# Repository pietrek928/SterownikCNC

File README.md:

# SterownikCNC
Sterownik do frezarki CNC

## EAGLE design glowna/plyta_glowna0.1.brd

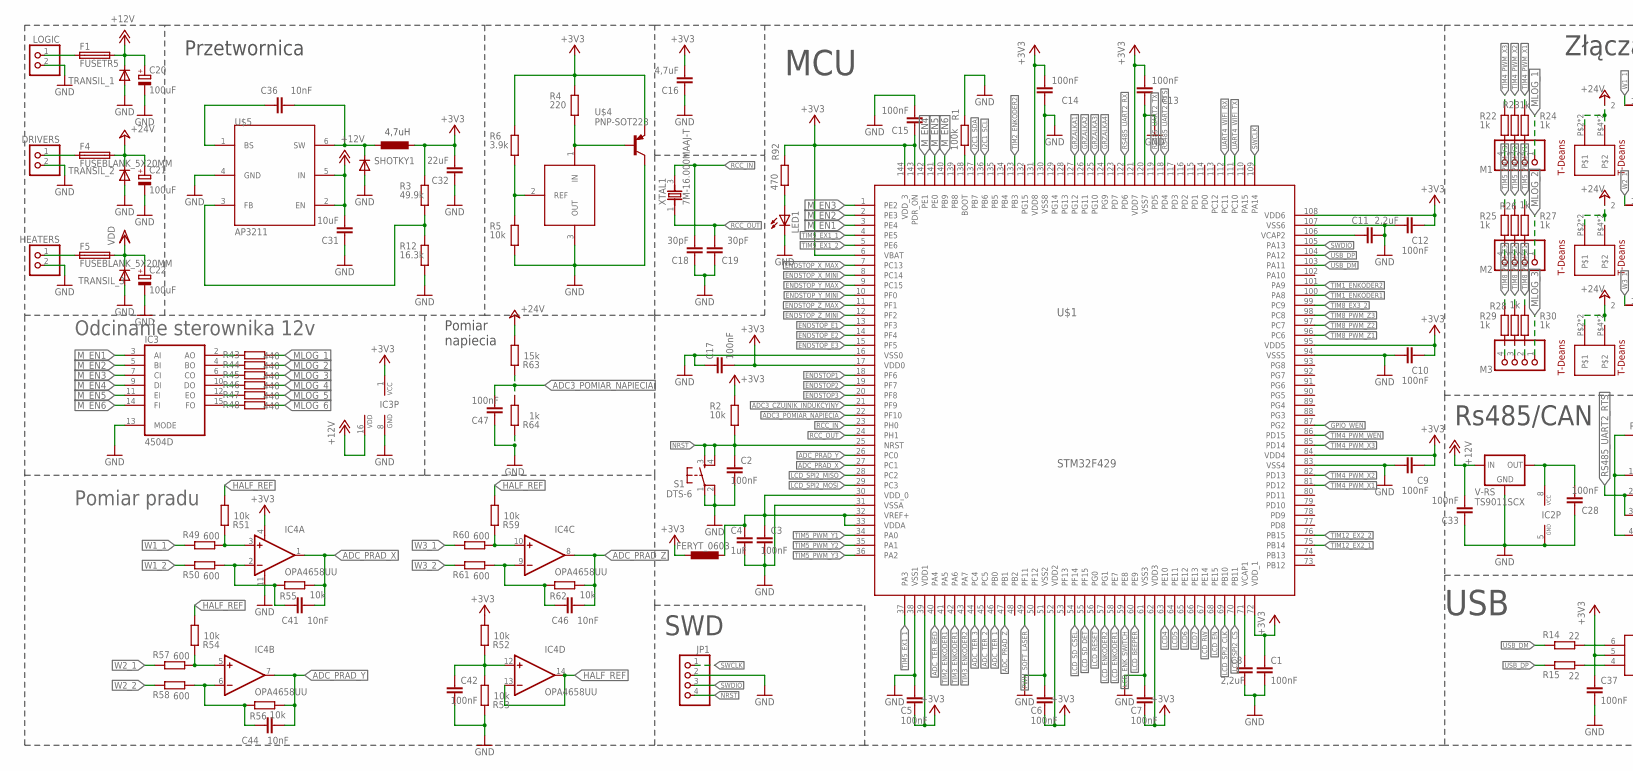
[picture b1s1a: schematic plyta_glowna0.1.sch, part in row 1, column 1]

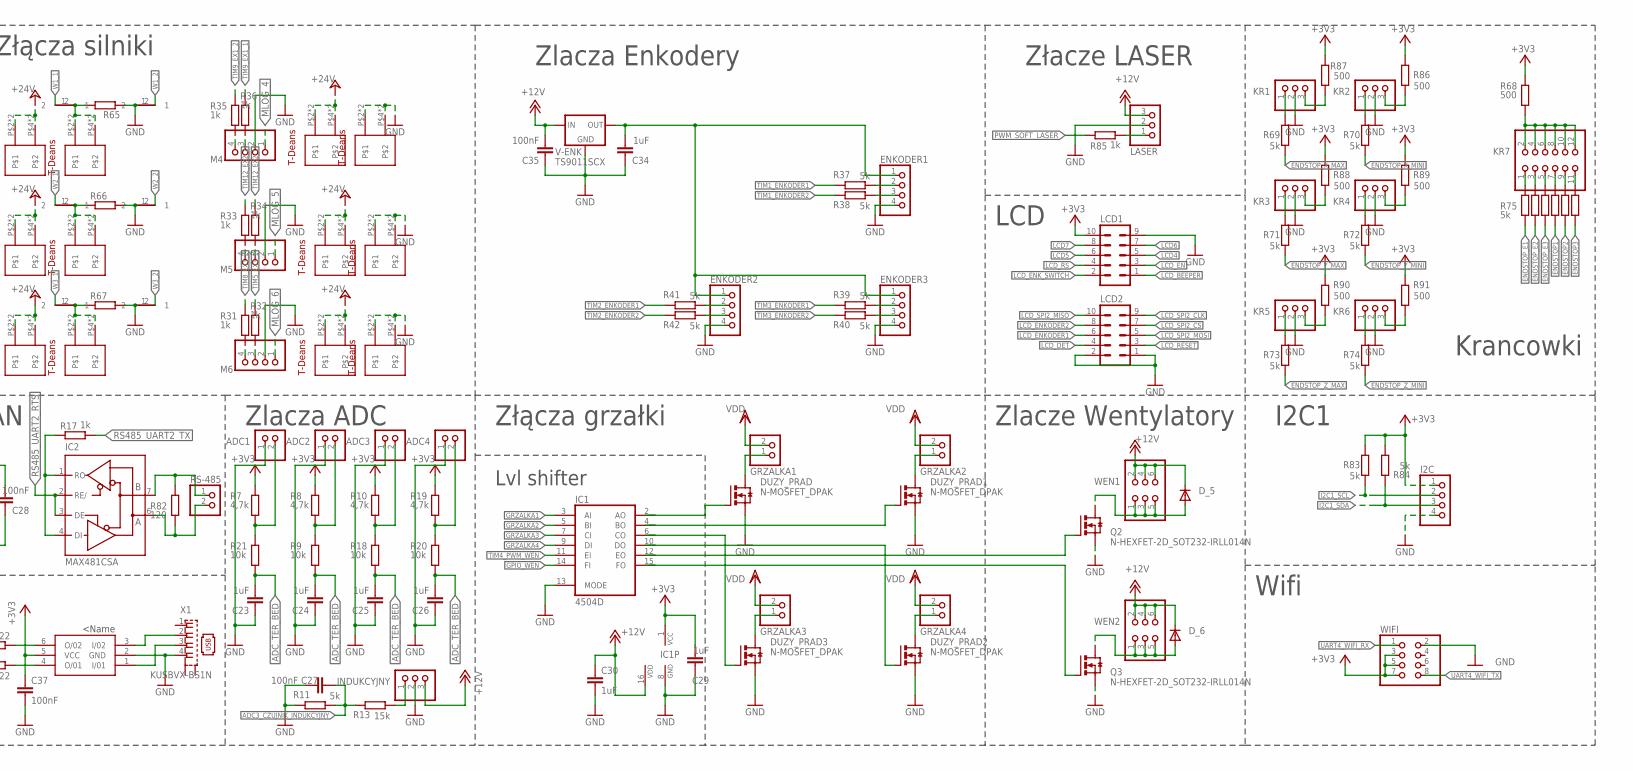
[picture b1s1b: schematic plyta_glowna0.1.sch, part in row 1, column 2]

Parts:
1, 2, 3, 4, 5, 6, 7, 8, 9, 10, 11, 12: PLYTKA_T
4,7UH: FERYT_0603; R0603
ADC1, ADC2, ADC3, ADC4: PINHD-1X2; 1X02
C1, C2, C3, C5, C6, C7, C9, C10, C12, C13, C14, C15, C17, C27, C28, C33, C35, C37, C42, C47: 100nF; C0603
C4, C23, C24, C25, C26, C29, C30, C34: 1uF; C0603
C8, C11: 2,2uF; C0603
C16: 4,7uF; C0603
C18, C19: 30pF; C0603
C20, C21, C22: 100uF; UD-8X10_NICHICON
C31: 10uF; C0603
C32: 22uF; C0603
C36, C41, C44, C46: 10nF; C0603
DRIVERS: PINHD-1X2; 1X02
DUZY_PRAD, DUZY_PRAD1, DUZY_PRAD2, DUZY_PRAD3: N-MOSFET_DPAK; D-PAK_TO252AA
D_5, D_6: DIODE-DO-214AC; DO-214AC
ENKODER1, ENKODER2, ENKODER3: PINHD-1X4; 1X04
F1: FUSETR5; TR5
F4, F5: FUSEBLANK_5X20MM; FUSE_HOLDER_5X20MM
GRZALKA1, GRZALKA2, GRZALKA3, GRZALKA4: PINHD-1X2; 1X02
HEATERS: PINHD-1X2; 1X02
I2C: PINHD-1X4; 1X04
IC1, IC3: 4504D; SO16
IC2: MAX481CSA; SO08
IC4: OPA4658UU; SO14
INDUKCYJNY: PINHD-1X3; 1X03
JP1: PINHD-1X4; 1X04
KR1, KR2, KR3, KR4, KR5, KR6: PINHD-1X3; 1X03
KR7: PINHD-2X6; 2X06
LASER: PINHD-1X3; 1X03
LCD1, LCD2: ML10
LED1: LEDSML0603; SML0603
LOGIC: PINHD-1X2; 1X02
M1, M2, M3, M4, M5, M6: PINHD-1X4; 1X04
Q2, Q3: N-HEXFET-2D_SOT232-IRLL014N; SOT223
R1: 100k; R0603
R2, R5, R9, R18, R20, R21, R51, R52, R53, R54, R55, R56, R59, R62: 10k; R0603
R3: 49.9k; R0603
R4: 220; R0603
R6: 3.9k; R0603
R7, R8, R10, R19: 4,7k; R0603
R11, R37, R38, R39, R40, R41, R42, R69, R70, R71, R72, R73, R74, R75, R76, R77, R78, R79, R80, R83, R84: 5k; R0603
R12: 16.3k; R0603
R13, R63: 15k; R0603
R14, R15: 22; R0603
R17, R22, R23, R24, R25, R26, R27, R28, R29, R30, R31, R32, R33, R34, R35, R36, R64, R85: 1k; R0603
R43, R44, R45, R46, R47, R48: 440; R0603
R49, R50, R57, R58, R60, R61: 600; R0603
R65, R66, R67: R-EU_R2512; R2512
R68, R86, R87, R88, R89, R90, R91: 500; R0603
R82: 120; R0603
R92: 470; R0603
RS-485: PINHD-1X2; 1X02
S1: DTS-6
SHOTKY1: DIODE-DO-214AC; DO-214AC
TRANSIL_1, TRANSIL_2, TRANSIL_3: DIODE-DO-214AC; DO-214AC
U$1: STM32F429; SQFP-S-20X20-144
U$2: FERYT_0603; R0603
U$3: TL431AIDBZR; SOT23
U$4: PNP-SOT223; SOT223
U$5: AP3211; TSOT23
U$6: USBLC6-2; SOT95P275X110-6N
U$20, U$21, U$22, U$23, U$24, U$25: SEPARATOR
V-ENK: TS9011SCX; SOT23
V-RS: TS9011SCX; SOT23
WEN1, WEN2: PINHD-2X3; 2X03
WIFI: PINHD-2X4; 2X04
X1: KUSBVX-BS1N
XTAL1: 7M-16.000MAAJ-T; TXC_7M-16.000MAAJ-T

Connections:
+3V3: 4,7UH.2, C1.1, C5.2, C6.2, C7.2, C9.2, C10.2, C12.2, C13.2, C14.2, C15.1, C16.2, C17.2, C29.2, C32.2, C37.1, I2C.1, IC1.1 (VCC), IC3.1 (VCC), IC4.4 (V+), LCD1.10, R2.1, R3.1, R4.1, R6.1, R7.1, R8.1, R10.1, R19.1, R52.2, R68.2, R83.2, R84.2, R86.1, R87.1, R88.1, R89.1, R90.1, R91.1, R92.1, U$1.6 (VBAT), U$1.17 (VDD0), U$1.39 (VDD1), U$1.52 (VDD2), U$1.62 (VDD3), U$1.72 (VDD_1), U$1.84 (VDD4), U$1.95 (VDD5), U$1.108 (VDD6), U$1.121 (VDD7), U$1.131 (VDD8), U$1.143 (PDR_ON), U$1.144 (VDD_3), U$2.1, U$4.3 (E), U$6.5 (VCC), WIFI.3, WIFI.5, WIFI.7
+12V: C20.+, C30.1, C31.2, C33.2, C35.2, D_5.C, D_6.C, F1.2, IC1.16 (VDD), IC3.16 (VDD), INDUKCYJNY.3, LASER.3, TRANSIL_1.C, U$5.2 (EN), U$5.5 (IN), V-ENK.3 (IN), V-RS.3 (IN), WEN1.2, WEN1.4, WEN1.6, WEN2.2, WEN2.4, WEN2.6
+24V: 1.P$2, 1.P$3, 1.P$4, 1.P$5, 3.P$2, 3.P$3, 3.P$4, 3.P$5, 5.P$2, 5.P$3, 5.P$4, 5.P$5, 7.P$2, 7.P$3, 7.P$4, 7.P$5, 9.P$2, 9.P$3, 9.P$4, 9.P$5, 11.P$2, 11.P$3, 11.P$4, 11.P$5, C21.+, F4.2, R63.2, TRANSIL_2.C
ADC3_CZUJNIK_INDUKCYJNY: U$1.21 (PF9)
ADC3_POMIAR_NAPIECIA: C47.2, R63.1, R64.2, U$1.22 (PF10)
ADC_PRAD_X: C41.2, IC4.1 (OUT), R55.1, U$1.27 (PC1)
ADC_PRAD_Y: C44.2, IC4.7 (OUT), R56.1, U$1.26 (PC0)
ADC_PRAD_Z: C46.2, IC4.8 (OUT), R62.1, U$1.47 (PB1)
ADC_TER_1: U$1.46 (PB0)
ADC_TER_2: U$1.45 (PC5)
ADC_TER_3: U$1.44 (PC4)
ADC_TER_BED: C23.2, C24.2, C25.2, C26.2, R9.2, R18.2, R20.2, R21.2, U$1.40 (PA4)
ENDSTOP1: R78.2, U$1.18 (PF6)
ENDSTOP2: R79.2, U$1.19 (PF7)
ENDSTOP3: R80.2, U$1.20 (PF8)
ENDSTOP_E1: R75.2, U$1.13 (PF3)
ENDSTOP_E2: R76.2, U$1.14 (PF4)
ENDSTOP_E3: R77.2, U$1.15 (PF5)
ENDSTOP_X_MAX: R69.1, U$1.7 (PC13)
ENDSTOP_X_MINI: R70.1, U$1.8 (PC14)
ENDSTOP_Y_MAX: R71.1, U$1.9 (PC15)
ENDSTOP_Y_MINI: R72.1, U$1.10 (PF0)
ENDSTOP_Z_MAX: R73.1, U$1.11 (PF1)
ENDSTOP_Z_MINI: R74.1, U$1.12 (PF2)
GND: 8.P$2, 8.P$3, 8.P$4, 8.P$5, 10.P$2, 10.P$3, 10.P$4, 10.P$5, 12.P$2, 12.P$3, 12.P$4, 12.P$5, ADC1.1, ADC2.1, ADC3.1, ADC4.1, C1.2, C2.2, C3.2, C4.2, C5.1, C6.1, C7.1, C8.2, C9.1, C10.1, C11.2, C12.1, C13.1, C14.1, C15.2, C16.1, C17.1, C18.1, C19.1, C20.-, C21.-, C22.-, C23.1, C24.1, C25.1, C26.1, C27.2, C28.1, C29.1, C30.2, C31.1, C32.1, C33.1, C34.1, C35.1, C37.2, C42.2, C47.1, DRIVERS.2, DUZY_PRAD.3 (S), DUZY_PRAD1.3 (S), DUZY_PRAD2.3 (S), DUZY_PRAD3.3 (S), ENKODER1.4, ENKODER2.4, ENKODER3.4, HEATERS.2, I2C.4, IC1.8 (GND), IC1.13 (MODE), IC2.5 (GND), IC3.8 (GND), IC3.13 (MODE), IC4.11 (V-), INDUKCYJNY.2, JP1.2, KR1.2, KR2.2, KR3.2, KR4.2, KR5.2, KR6.2, LASER.2, LCD1.9, LCD2.1, LCD2.2, LED1.C, LOGIC.2, M4.2, M5.2, M6.2, Q2.3 (S), Q3.3 (S), R1.1, R5.2, R11.1, R12.2, R53.1, R64.1, R65.1, R66.2, R67.2, S1.1, S1.2, SHOTKY1.A, TRANSIL_1.A, TRANSIL_2.A, TRANSIL_3.A, U$1.16 (VSS0), U$1.31 (VSSA), U$1.38 (VSS1), U$1.51 (VSS2), U$1.61 (VSS3), U$1.83 (VSS4), U$1.94 (VSS5), U$1.107 (VSS6), U$1.120 (VSS7), U$1.130 (VSS8), U$3.3 (OUT), U$4.2 (C), U$4.4 (C), U$5.4 (GND), U$6.2 (GND), U$20.1, U$21.1, U$22.1, V-ENK.1 (GND), V-RS.1 (GND), WIFI.2, X1.4
GPIO_WEN: IC1.14 (FI), U$1.87 (PG2)
GRZALKA1: IC1.3 (AI), U$1.127 (PG12)
GRZALKA2: IC1.5 (BI), U$1.126 (PG11)
GRZALKA3: IC1.7 (CI), U$1.125 (PG10)
GRZALKA4: IC1.9 (DI), U$1.124 (PG9)
HALF_REF: IC4.13 (-IN), IC4.14 (OUT), R51.2, R54.2, R59.2
I2C1_SCL: I2C.2, R83.1, U$1.136 (PB6)
I2C1_SDA: I2C.3, R84.1, U$1.137 (PB7)
LCD4: LCD1.5, U$1.63 (PE10)
LCD5: LCD1.6, U$1.64 (PE11)
LCD6: LCD1.7, U$1.65 (PE12)
LCD7: LCD1.8, U$1.66 (PE13)
LCD_BEEPER: LCD1.1, U$1.60 (PE9)
LCD_DET: LCD2.4
LCD_EN: LCD1.3, U$1.68 (PE15)
LCD_ENKODER1: LCD2.6, U$1.58 (PE7)
LCD_ENKODER2: LCD2.8, U$1.57 (PG1)
LCD_ENK_SWITCH: LCD1.2, U$1.59 (PE8)
LCD_RESET: LCD2.3, U$1.56 (PG0)
LCD_RS: LCD1.4
LCD_RW: U$1.67 (PE14)
LCD_SD_CSEL: U$1.54 (PF14)
LCD_SD_DET: U$1.55 (PF15)
LCD_SPI2_CLK: LCD2.9, U$1.69 (PB10)
LCD_SPI2_CS: LCD2.7, U$1.70 (PB11)
LCD_SPI2_MISO: LCD2.10, U$1.28 (PC2)
LCD_SPI2_MOSI: LCD2.5, U$1.29 (PC3)
MLOG_1: M1.1, R43.2
MLOG_2: M2.1, R44.2
MLOG_3: M3.1, R45.2
MLOG_4: M4.1, R46.2
MLOG_5: M5.1, R47.2
MLOG_6: M6.1, R48.2
M_EN1: IC3.3 (AI)
M_EN3: U$1.1 (PE2)
unnamed: 4,7UH.1, C36.1, SHOTKY1.C, U$5.6 (SW)
unnamed: C8.1, U$1.71 (VCAP1)
unnamed: R3.2, R12.1, U$5.3 (FB)
unnamed: R14.2, U$6.6 (O/02)
unnamed: C3.1, C4.1, U$1.30 (VDD_0), U$1.32 (VREF+), U$1.33 (VDDA), U$2.2
unnamed: R5.1, R6.2, U$3.2 (REF)
unnamed: F1.1, LOGIC.1
unnamed: DRIVERS.1, F4.1
unnamed: R4.2, U$3.1 (IN), U$4.1 (B)
unnamed: F5.1, HEATERS.1
unnamed: D_6.A, Q3.2 (D), Q3.4 (D), WEN2.1, WEN2.3, WEN2.5
unnamed: DUZY_PRAD.4 (D), GRZALKA1.1
unnamed: R15.2, U$6.4 (O/01)
unnamed: D_5.A, Q2.2 (D), Q2.4 (D), WEN1.1, WEN1.3, WEN1.5
unnamed: U$6.1 (I/01), X1.3
unnamed: DUZY_PRAD1.4 (D), GRZALKA2.1
unnamed: DUZY_PRAD2.4 (D), GRZALKA4.1
unnamed: C11.1, U$1.106 (VCAP2)
unnamed: DUZY_PRAD3.4 (D), GRZALKA3.1
unnamed: DUZY_PRAD.1 (G), IC1.2 (AO)
unnamed: KR1.1, R69.2
unnamed: LASER.1, R85.1
unnamed: KR3.1, R71.2
unnamed: KR2.1, R70.2
unnamed: R1.2, U$1.138 (BOOT)
unnamed: KR4.1, R72.2
unnamed: KR6.1, R74.2
unnamed: KR5.1, R73.2
unnamed: IC2.7 (B), R82.1, RS-485.1
unnamed: IC2.6 (A), R82.2, RS-485.2
unnamed: KR7.1, R75.1
unnamed: DUZY_PRAD1.1 (G), IC1.4 (BO)
unnamed: DUZY_PRAD3.1 (G), IC1.6 (CO)
unnamed: DUZY_PRAD2.1 (G), IC1.10 (DO)
unnamed: IC1.12 (EO), Q2.1 (G)
unnamed: IC1.15 (FO), Q3.1 (G)
unnamed: INDUKCYJNY.1, R13.2
unnamed: C36.2, U$5.1 (BS)
unnamed: C28.2, IC2.8 (VCC), V-RS.2 (OUT)
unnamed: M1.4, R22.2
unnamed: ADC2.2, R8.2, R9.1
unnamed: ADC1.2, R7.2, R21.1
unnamed: ADC3.2, R10.2, R18.1
unnamed: M1.3, R23.2
unnamed: M1.2, R24.2
unnamed: ADC4.2, R19.2, R20.1
unnamed: M6.4, R31.2
unnamed: M2.4, R25.2
unnamed: M2.3, R26.2
unnamed: M6.3, R32.2
unnamed: M3.4, R29.2
unnamed: M3.3, R28.2
unnamed: U$6.3 (I/02), X1.2
unnamed: M5.4, R33.2
unnamed: M5.3, R34.2
unnamed: M2.2, R27.2
unnamed: M4.4, R35.2
unnamed: M4.3, R36.2
unnamed: ENKODER1.2, R37.2
unnamed: ENKODER1.3, R38.2
unnamed: ENKODER3.2, R39.2
unnamed: ENKODER3.3, R40.2
unnamed: ENKODER2.2, R41.2
unnamed: ENKODER2.3, R42.2
unnamed: IC3.2 (AO), R43.1
unnamed: IC3.4 (BO), R44.1
unnamed: IC3.6 (CO), R45.1
unnamed: IC3.10 (DO), R46.1
unnamed: IC3.12 (EO), R47.1
unnamed: IC3.15 (FO), R48.1
unnamed: IC4.3 (+IN), R49.2, R51.1
unnamed: C42.1, IC4.12 (+IN), R52.1, R53.2
unnamed: C41.1, IC4.2 (-IN), R50.2, R55.2
unnamed: C46.1, IC4.9 (-IN), R61.2, R62.2
unnamed: 2.P$2, 2.P$3, 2.P$4, 2.P$5, R65.2, U$23.2
unnamed: 4.P$2, 4.P$3, 4.P$4, 4.P$5, R66.1, U$24.2
unnamed: IC4.10 (+IN), R59.1, R60.2
unnamed: C44.1, IC4.6 (-IN), R56.2, R58.2
unnamed: IC4.5 (+IN), R54.1, R57.2
unnamed: 6.P$2, 6.P$3, 6.P$4, 6.P$5, R67.1, U$25.2
unnamed: KR7.3, R76.1
unnamed: KR7.5, R77.1
unnamed: KR7.7, R78.1
unnamed: KR7.9, R79.1
unnamed: KR7.11, R80.1
unnamed: KR7.2, KR7.4, KR7.6, KR7.8, KR7.10, KR7.12, R68.1
unnamed: KR1.3, R87.2
unnamed: KR2.3, R86.2
unnamed: KR3.3, R88.2
unnamed: KR4.3, R89.2
unnamed: KR5.3, R90.2
unnamed: KR6.3, R91.2
unnamed: C27.1, R11.2, R13.1
unnamed: LED1.A, R92.2
unnamed: C34.2, ENKODER1.1, ENKODER2.1, ENKODER3.1, V-ENK.2 (OUT)
NRST: C2.1, JP1.4, R2.2, S1.3, S1.4, U$1.25 (NRST)
PWM_SOFT_LASER: R85.2, U$1.49 (PF11)
RCC_IN: C18.2, U$1.23 (PH0), XTAL1.3
RCC_OUT: C19.2, U$1.24 (PH1), XTAL1.1
RS485_UART2_RTS: IC2.2 (RE/), IC2.3 (DE), U$1.118 (PD4)
RS485_UART2_RX: U$1.122 (PD6)
RS485_UART2_TX: IC2.1 (RO), IC2.4 (DI), R17.1, R17.2, U$1.119 (PD5)
SWCLK: JP1.1, U$1.109 (PA14)
SWDIO: JP1.3, U$1.105 (PA13)
TIM1_ENKODER1: R37.1, U$1.100 (PA8)
TIM1_ENKODER2: R38.1, U$1.101 (PA9)
TIM2_ENKODER1: R41.1, U$1.41 (PA5)
TIM2_ENKODER2: R42.1, U$1.133 (PB3)
TIM3_ENKODER1: R39.1, U$1.42 (PA6)
TIM3_ENKODER2: R40.1, U$1.43 (PA7)
TIM4_PWM_WEN: IC1.11 (EI), U$1.86 (PD15)
TIM4_PWM_X1: R24.1, U$1.81 (PD12)
TIM4_PWM_X2: R23.1, U$1.82 (PD13)
TIM4_PWM_X3: R22.1, U$1.85 (PD14)
TIM5_EX1_1: U$1.37 (PA3)
TIM5_EX3_1: R32.1
TIM5_PWM_Y1: R27.1, U$1.34 (PA0)
TIM5_PWM_Y2: R26.1, U$1.35 (PA1)
TIM5_PWM_Y3: R25.1, U$1.36 (PA2)
TIM8_EX3_2: R31.1, U$1.99 (PC9)
TIM8_PWM_Z1: M3.2, R30.1, R30.2, U$1.96 (PC6)
TIM8_PWM_Z2: R28.1, U$1.97 (PC7)
TIM8_PWM_Z3: R29.1, U$1.98 (PC8)
TIM9_EX1_1: R36.1, U$1.4 (PE5)
TIM9_EX1_2: R35.1, U$1.5 (PE6)
TIM12_EX2_1: R34.1, U$1.75 (PB14)
TIM12_EX2_2: R33.1, U$1.76 (PB15)
UART4_WIFI_RX: U$1.112 (PC11), WIFI.1
UART4_WIFI_TX: U$1.111 (PC10), WIFI.8
USB_DM: R14.1, U$1.103 (PA11)
USB_DP: R15.1, U$1.104 (PA12)
VDD: C22.+, F5.2, GRZALKA1.2, GRZALKA2.2, GRZALKA3.2, GRZALKA4.2, TRANSIL_3.C
W1_1: R49.1, U$23.1
W1_2: R50.1, U$20.2
W2_1: R57.1, U$24.1
W2_2: R58.1, U$21.2
W3_1: R60.1, U$25.1
W3_2: R61.1, U$22.2

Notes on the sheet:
MCU
Złącza silniki
Złącza grzałki
Zlacza ADC
Zlacza Enkodery
Rs485/CAN
Złacze LASER
Zlacze Wentylatory
USB
LCD
Krancowki
I2C1
Wifi
Lvl shifter
Pomiar napiecia
Pomiar pradu
Odcinanie sterownika 12v
SWD
Przetwornica
4,7uH

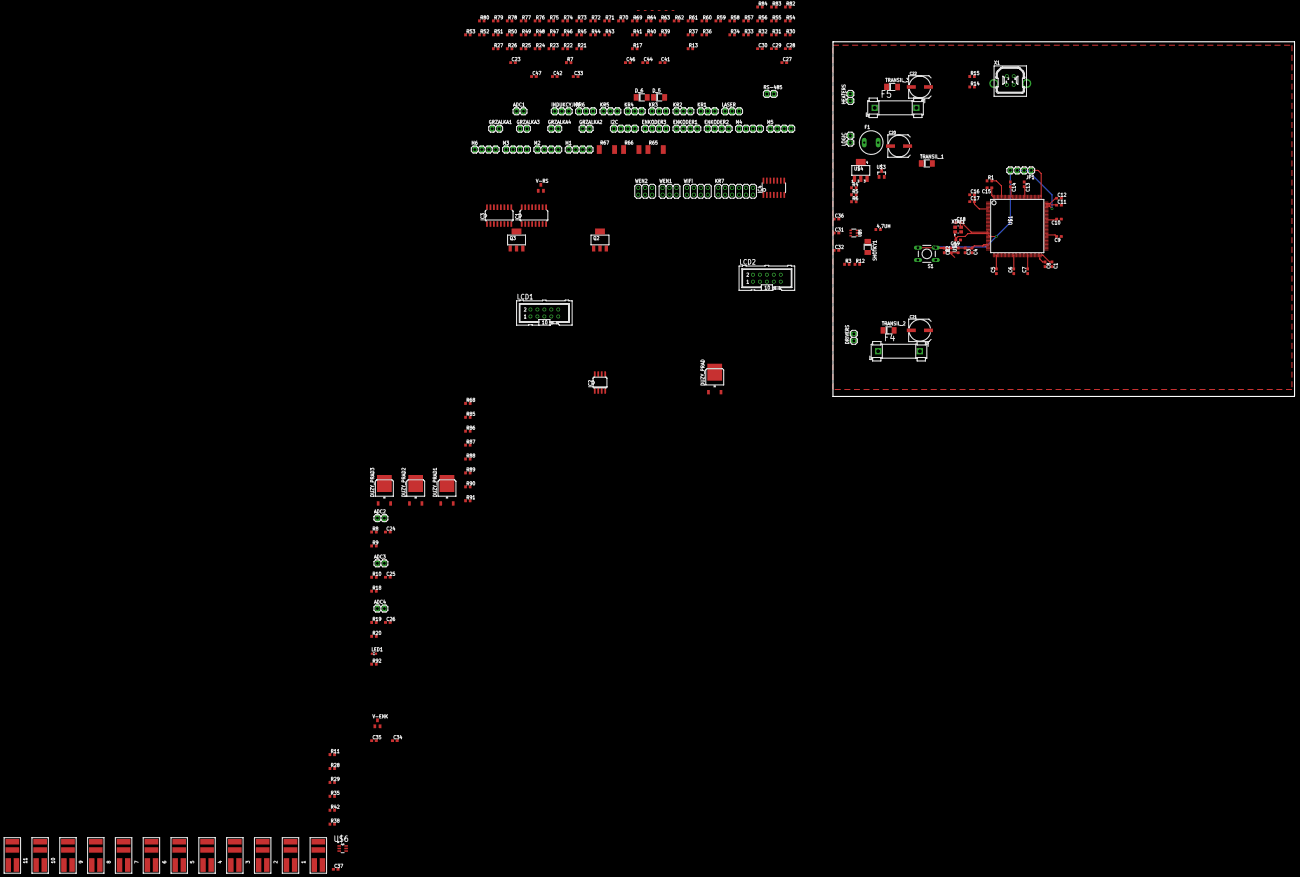
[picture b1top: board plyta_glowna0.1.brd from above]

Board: 2 copper layers, 168.6 x 129.5 mm, 219 parts (0 on the bottom side), 184 nets.

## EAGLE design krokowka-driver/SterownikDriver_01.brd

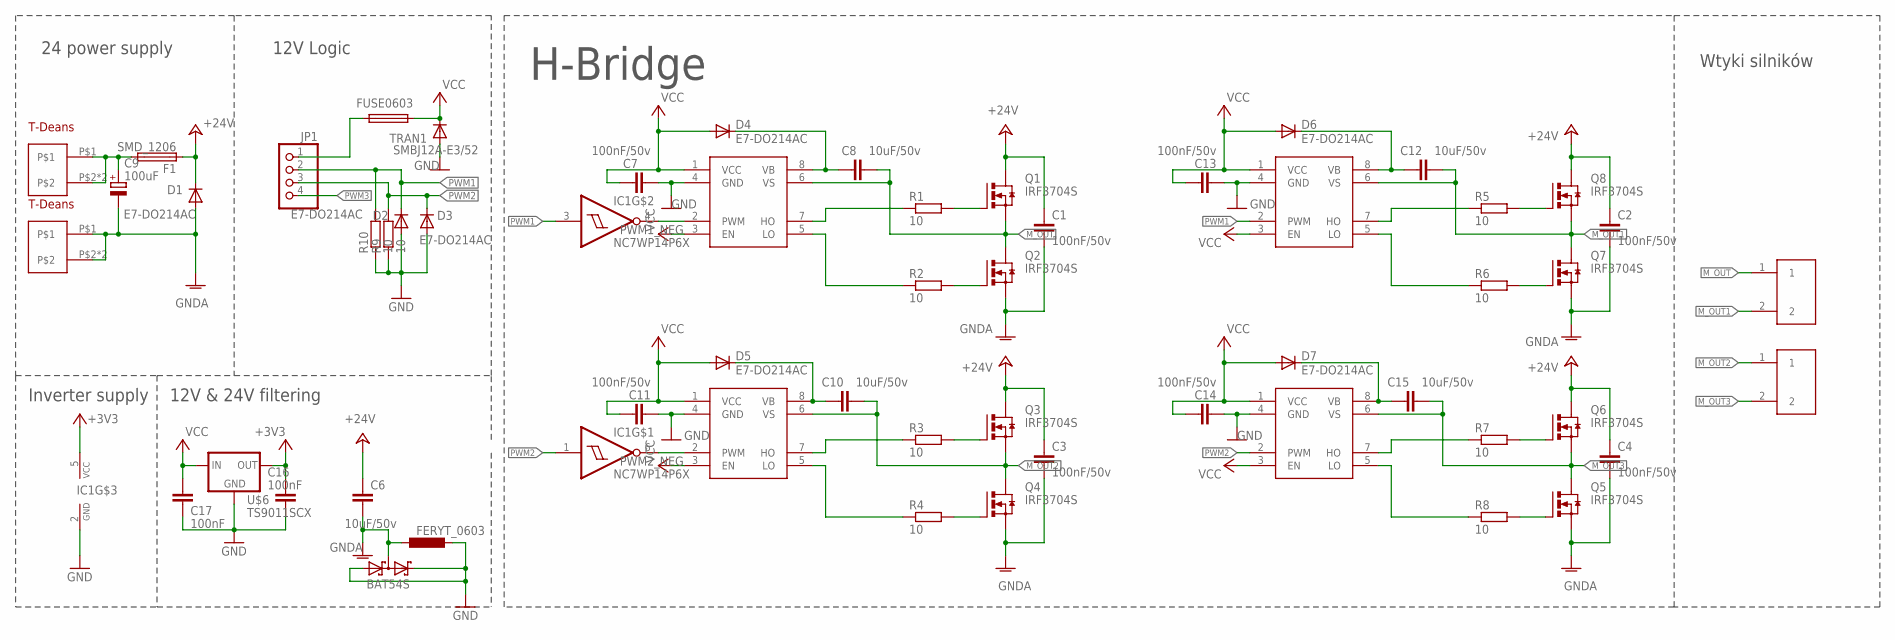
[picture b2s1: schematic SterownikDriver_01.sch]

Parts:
C1, C2, C3, C4, C7, C11, C13, C14: 100nF/50v; C0603K
C6, C8, C10, C12, C15: 10uF/50v; C0603K
C9: 100uF; 140CLH-0810
C16, C17: 100nF; C0603K
D1, D2, D3, D4, D5, D6, D7: E7-DO214AC; DO214AC
D8: BAT54S; SOT23
F1: SMD_1206; 1026
GND: T-DEANS
IC1: NC7WP14P6X; SOT65P210X110-6AN_SC88_SC70-6
JP1: PINHD-1X4; 1X04
Q1, Q2, Q3, Q4, Q5, Q6, Q7, Q8: IRF3704S; D2PACK
R1, R2, R3, R4, R5, R6, R7, R8, R9, R10: 10; R0603
TRAN1: SMBJ12A-E3/52; DO214AA
U1, U2, U3, U4: IR2104; SO08
U$3: FUSE0603; 0603
U$4: FERYT_0603; R0603
U$6: TS9011SCX; SOT23
U$7, U$9: PTB-02_5.08MM; PTB-5.08MM-02
VCC: T-DEANS

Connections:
+3V3: C16.1, IC1.5 (VCC), U$6.2 (OUT)
+24V: C1.1, C2.1, C3.1, C4.1, C6.1, D1.C, F1.P$1 (1), Q1.2 (D), Q3.2 (D), Q6.2 (D), Q8.2 (D)
F2: JP1.1, U$3.1
GND: C7.2, C11.2, C13.2, C14.2, C16.2, C17.2, D2.A, D3.A, D8.1 (A1), D8.2 (C2), IC1.2 (GND), R9.1, R10.1, TRAN1.A, U1.4 (GND), U2.4 (GND), U3.4 (GND), U4.4 (GND), U$4.2, U$6.1 (GND)
GNDA: C1.2, C2.2, C3.2, C4.2, C6.2, C9.-, D1.A, D8.3 (C1A2), GND.P$1, GND.P$2, GND.P$3, Q2.3 (S), Q4.3 (S), Q5.3 (S), Q7.3 (S), U$4.1
M_OUT: C8.2, Q1.3 (S), Q2.2 (D), U1.6 (VS), U$7.1
M_OUT1: C12.2, Q7.2 (D), Q8.3 (S), U2.6 (VS), U$7.2
M_OUT2: C10.2, Q3.3 (S), Q4.2 (D), U3.6 (VS), U$9.1
M_OUT3: C15.2, Q5.2 (D), Q6.3 (S), U4.6 (VS), U$9.2
unnamed: Q1.1 (G), R1.2
unnamed: Q2.1 (G), R2.2
unnamed: R1.1, U1.7 (HO)
unnamed: R2.1, U1.5 (LO)
unnamed: R5.1, U2.7 (HO)
unnamed: R6.1, U2.5 (LO)
unnamed: Q7.1 (G), R6.2
unnamed: Q8.1 (G), R5.2
unnamed: C10.1, D5.C, U3.8 (VB)
unnamed: C9.+, F1.P$2 (2), VCC.P$1, VCC.P$2, VCC.P$3
unnamed: R3.1, U3.7 (HO)
unnamed: R4.1, U3.5 (LO)
unnamed: Q4.1 (G), R4.2
unnamed: Q3.1 (G), R3.2
unnamed: C15.1, D7.C, U4.8 (VB)
unnamed: R7.1, U4.7 (HO)
unnamed: R8.1, U4.5 (LO)
unnamed: Q5.1 (G), R8.2
unnamed: Q6.1 (G), R7.2
unnamed: C8.1, D4.C, U1.8 (VB)
unnamed: C12.1, D6.C, U2.8 (VB)
PWM1: D2.C, IC1.3 (I), JP1.2, R10.2, U2.2 (PWM)
PWM1_NEG: IC1.4 (O), U1.2 (PWM)
PWM2: D3.C, IC1.1 (I), JP1.3, R9.2, U4.2 (PWM)
PWM2_NEG: IC1.6 (O), U3.2 (PWM)
PWM3: JP1.4
VCC: C7.1, C11.1, C13.1, C14.1, C17.1, D4.A, D5.A, D6.A, D7.A, TRAN1.C, U1.1 (VCC), U1.3 (EN), U2.1 (VCC), U2.3 (EN), U3.1 (VCC), U3.3 (EN), U4.1 (VCC), U4.3 (EN), U$3.2, U$6.3 (IN)

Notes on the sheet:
H-Bridge
Inverter supply
24 power supply
12V Logic
12V & 24V filtering
Wtyki silników

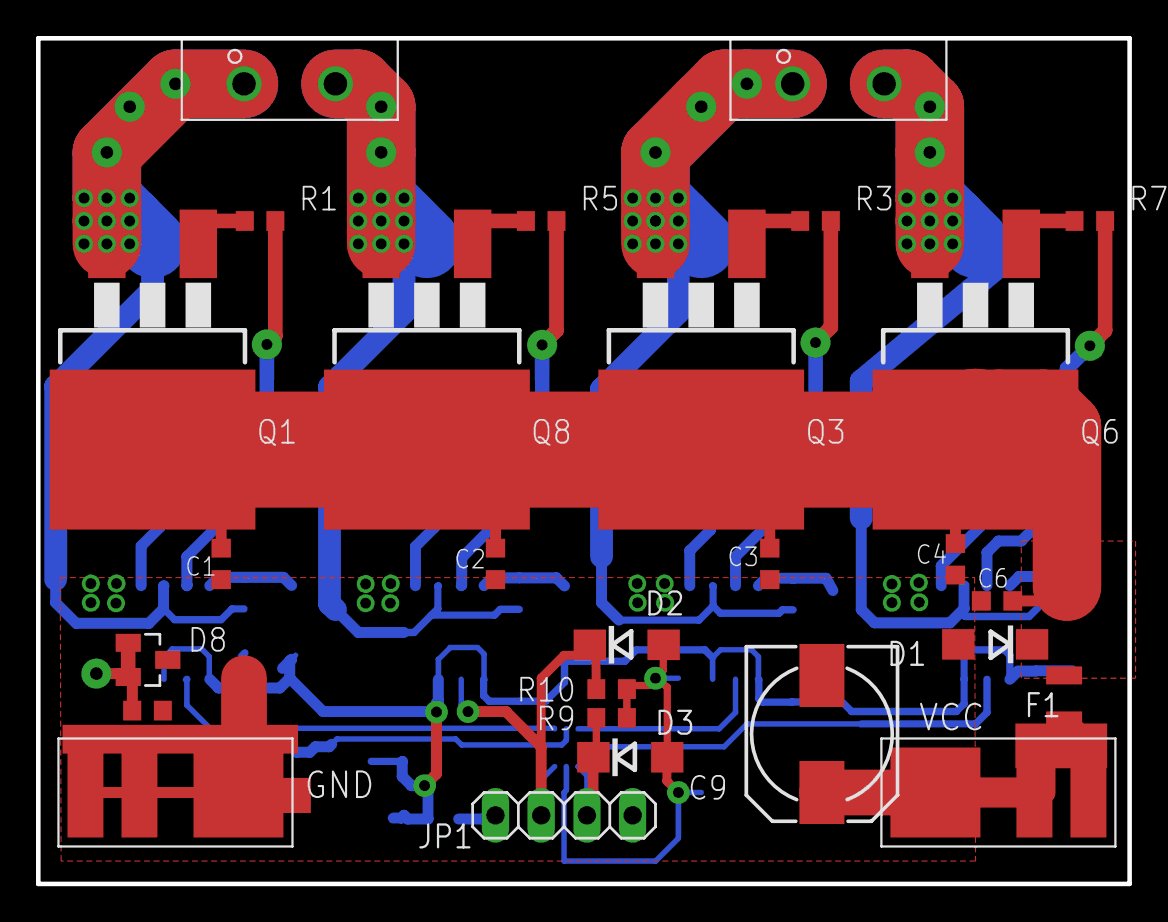
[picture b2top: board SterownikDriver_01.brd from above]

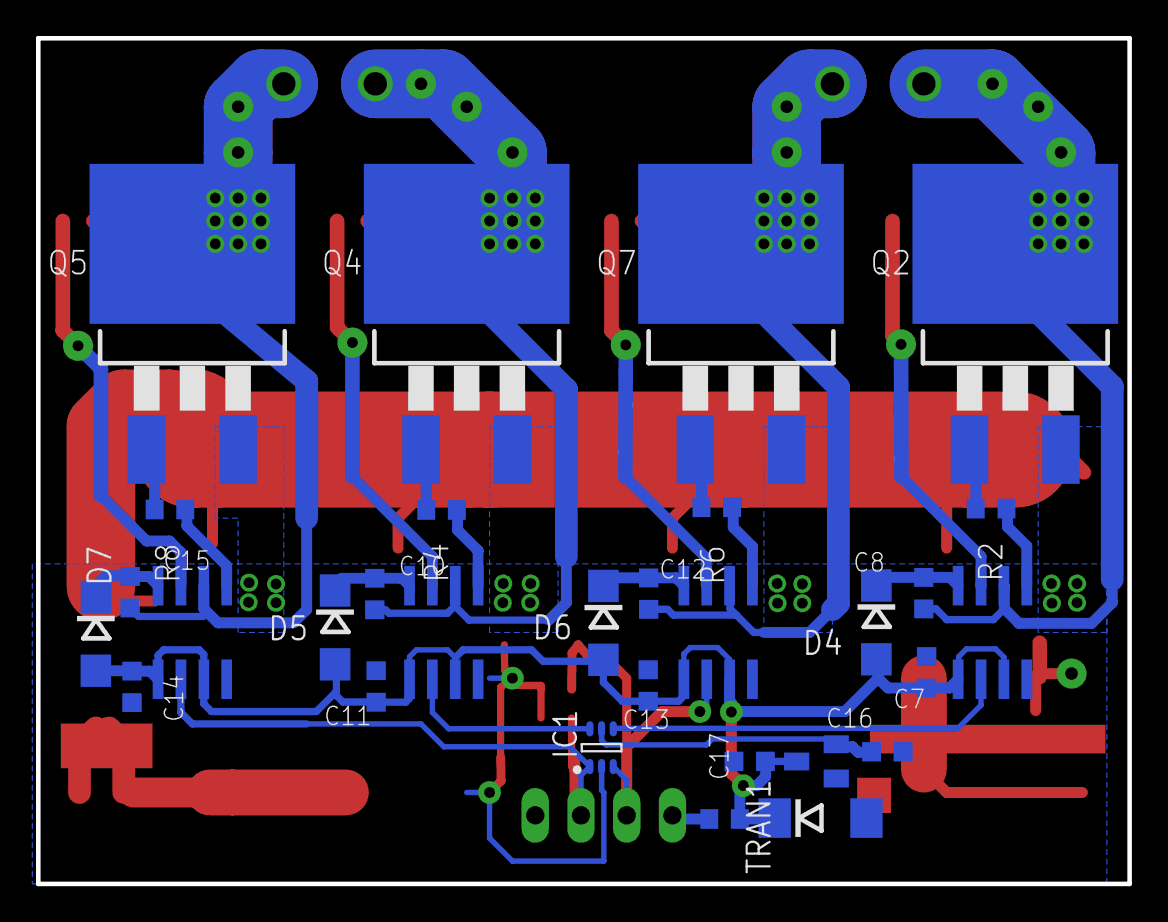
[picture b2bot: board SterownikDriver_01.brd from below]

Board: 2 copper layers, 60.6 x 47.0 mm, 57 parts (30 on the bottom side), 35 nets.

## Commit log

2016-12-25 opis
2016-12-25 Create LICENCE
2016-12-25 poprawilem inwerter invokiem
2016-12-26 poprawilem kodowanie w pliku bo bylo chujowe z maca
2016-12-26 poprawiony opis
2016-12-26 opis - stabilizator
2016-12-26 added krokowka-driver/
2016-12-27 Add existing file
2016-12-27 poprawilem
2016-12-27 test gita
2016-12-27 zbedne
2016-12-27 plytka
2016-12-28 to jest aktualny schemat
2016-12-28 niepotrzebne pliki
2016-12-30 zmina_30.12
2016-12-30 Nowa wersja, eagle cos zjebal
2016-12-30 bezpiecznik i elektrolit
2016-12-30 Version 0.1
2016-12-30 sprzatanie
2017-01-08 plyta glowna
2017-01-08 ferryt
2017-01-08 glowna
2017-01-09 Zmiana nazwy
2017-01-09 usuwam glowna
2017-01-09 znowu
2017-01-09 sprzatam
2017-01-09 indukcyjne
2017-01-09 level shifter
2017-01-09 rs i termistory
2017-01-09 kondensatory
2017-01-09 zabezpieczenia
2017-01-09 zabezpieczenie i filtr do enkoderow
2017-01-09 silniki - sterowanie
2017-01-09 pomiar pradu - koncepcja
2017-01-09 pomiar pradu - poprawiony
2017-01-09 pomiar pradu
2017-01-09 prad
2017-01-09 zmiana
2017-01-09 jebany git
2017-01-09 test
2017-01-09 biblioteka
2017-01-09 konczymy
2017-01-09 koniec?
2017-01-09 to juz jest koniec
2017-01-09 chyba twoj
2017-01-09 z mojej strony koniec
2017-01-09 krancowki-zabezpieczenia
2017-01-10 rezystorki w i2c
2017-01-13 wstepny schemat
2017-01-14 5v enkoder
2017-01-15 sprzątam
2017-01-27 ver 0.2
2017-01-30 Revert "0.2"
    This reverts commit 92bf75da2d5e0387fb4a98a264039f74cd3fbe12.
2017-02-09 Complete Ver 0.1
2017-07-11 Add files via upload
    test
